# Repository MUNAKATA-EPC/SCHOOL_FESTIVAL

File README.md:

# SCHOOL_FESTIVAL
文化祭で使用したプログラムです

PS3コントローラーの受信に関して

http://gijin77.blog.jp/archives/21966552.html

上記のWEBサイトを参考にしました。使用するESP32ライブラリに関してVer1.0.4以外のバージョンで動作確認が取れません。専用ソフトを使用して使用するM5stampのMACaddressをコントローラーに書き込む必要があります。Ps3.data.---の戻り値がスティックの角度となります。

Wii Balance Bordに関して

https://github.com/takeru/Wiimote/tree/BalanceBoard

上記のWEBサイトを参考にしました。ライブラリをインストールしてサンプルプログラムを実行します。weight［ーーー］の戻り値が各センサの重量となります。起動時に本体裏のリセットボタンを押す必要があります。

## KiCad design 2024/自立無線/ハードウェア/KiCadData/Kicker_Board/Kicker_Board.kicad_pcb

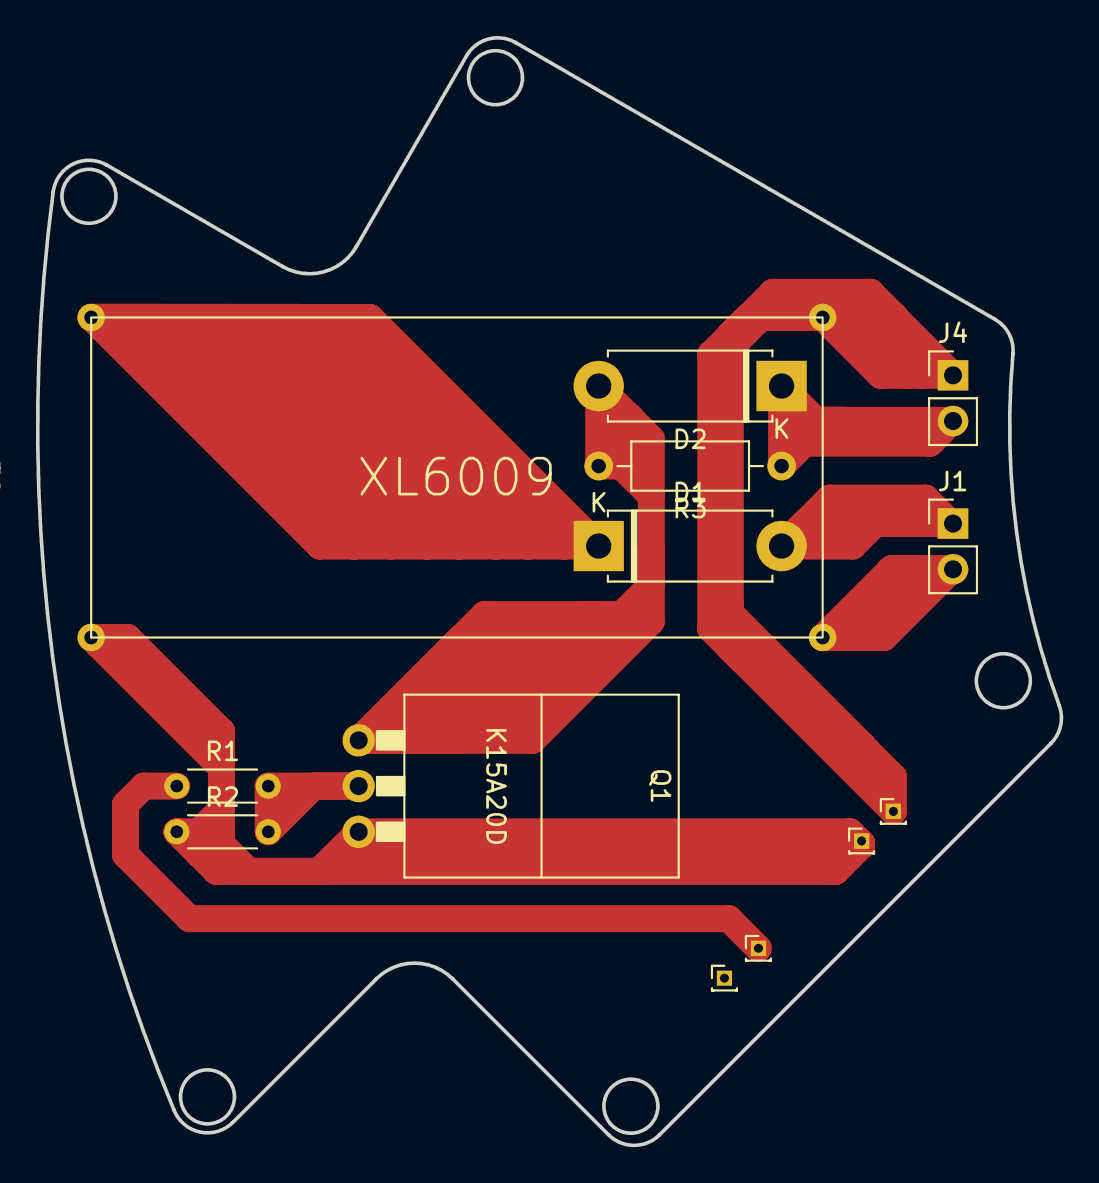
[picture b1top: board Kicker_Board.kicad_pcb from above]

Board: 2 copper layers, 56.9 x 61.5 mm, 9 parts (0 on the bottom side), 7 nets.

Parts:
D1, D2: D; D_5W_P10.16mm_Horizontal
J1, J4: Conn_01x02_Socket; PinHeader_1x02_P2.54mm_Vertical
Q1: NMOS; K15A20D
R1, R2: R; R_Axial_DIN0204_L3.6mm_D1.6mm_P5.08mm_Horizontal
R3: R; R_Axial_DIN0207_L6.3mm_D2.5mm_P10.16mm_Horizontal
U1: XL6009

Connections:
+12V: D1.2 (A), J1.1
GND: J1.2, Q1.3 (S), R2.1, U1.2 (IN-), U1.4 (OUT-)
unnamed: D1.1 (K), U1.1 (IN+)
unnamed: D2.2 (A), Q1.1 (D), R3.2
unnamed: D2.1 (K), J4.2, R3.1
unnamed: J4.1, U1.3 (OUT+)
unnamed: Q1.2 (G), R1.2, R2.2

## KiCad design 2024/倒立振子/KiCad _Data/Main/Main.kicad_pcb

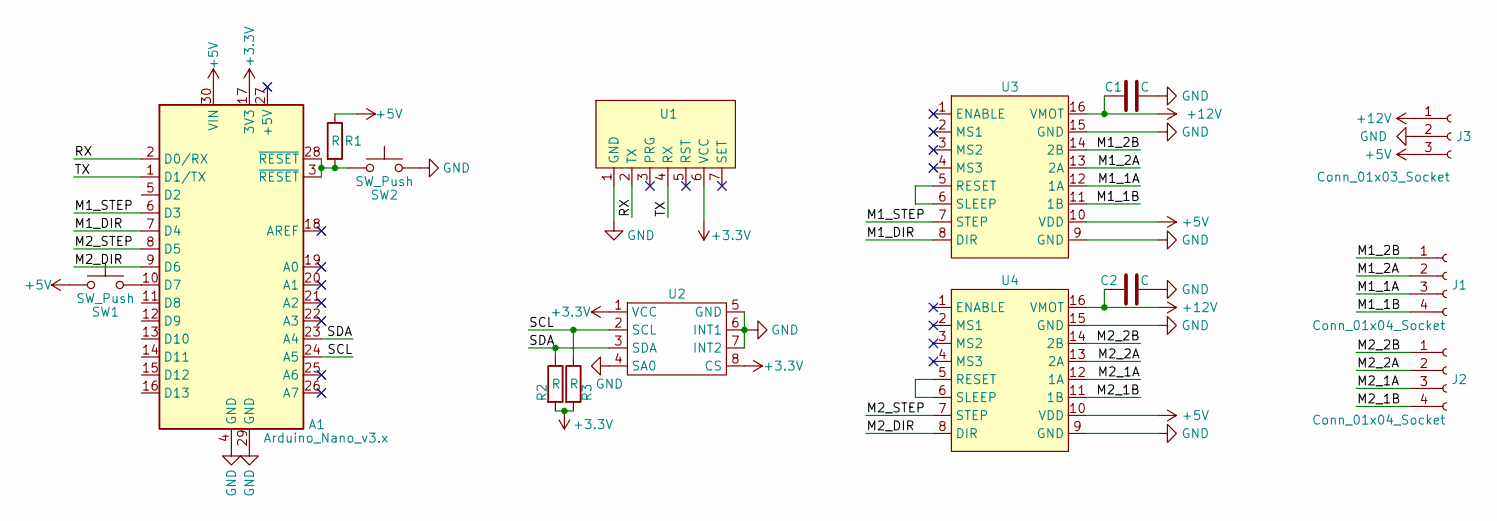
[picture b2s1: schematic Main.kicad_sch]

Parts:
A1: Arduino_Nano_v3.x; Arduino_Nano
C1, C2: C; CP_Radial_D5.0mm_P2.50mm
J1, J2: Conn_01x04_Socket; JST_XH_B4B-XH-A_1x04_P2.50mm_Vertical
J3: Conn_01x03_Socket; JST_XH_B3B-XH-A_1x03_P2.50mm_Vertical
R1, R2, R3: R; R_Axial_DIN0204_L3.6mm_D1.6mm_P5.08mm_Horizontal
SW1, SW2: SW_Push; SW_PUSH_6mm
U1: PinHeader_1x07_P2.54mm_Horizontal
U2: L3GD20H_Module
U3, U4: A4988

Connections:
+3.3V: A1.17 (3V3), R2.2, R3.2, U1.6 (VCC), U2.1 (VCC), U2.8 (CS)
+5V: A1.30 (VIN), J3.3, R1.1, SW1.1, U3.10 (VDD), U4.10 (VDD)
+12V: C1.2, C2.2, J3.1, U3.16 (VMOT), U4.16 (VMOT)
/M1_1A: J1.3, U3.12 (1A)
/M1_1B: J1.4, U3.11 (1B)
/M1_2A: J1.2, U3.13 (2A)
/M1_2B: J1.1, U3.14 (2B)
/M1_DIR: A1.7 (D4), U3.8 (DIR)
/M1_STEP: A1.6 (D3), U3.7 (STEP)
/M2_1A: J2.3, U4.12 (1A)
/M2_1B: J2.4, U4.11 (1B)
/M2_2A: J2.2, U4.13 (2A)
/M2_2B: J2.1, U4.14 (2B)
/M2_DIR: A1.9 (D6), U4.8 (DIR)
/M2_STEP: A1.8 (D5), U4.7 (STEP)
/RX: A1.2 (D0/RX), U1.2 (TX)
/SCL: A1.24 (A5), R3.1, U2.2 (SCL)
/SDA: A1.23 (A4), R2.1, U2.3 (SDA)
/TX: A1.1 (D1/TX), U1.4 (RX)
GND: A1.4 (GND), A1.29 (GND), C1.1, C2.1, J3.2, SW2.2, U1.1 (GND), U2.4 (SA0), U2.5 (GND), U2.6 (INT1), U2.7 (INT2), U3.9 (GND), U3.15 (GND), U4.9 (GND), U4.15 (GND)
unnamed: A1.10 (D7), SW1.2
unnamed: A1.3 (~RESET), A1.28 (~RESET), R1.2, SW2.1
unnamed: U3.5 (RESET), U3.6 (SLEEP)
unnamed: U4.5 (RESET), U4.6 (SLEEP)

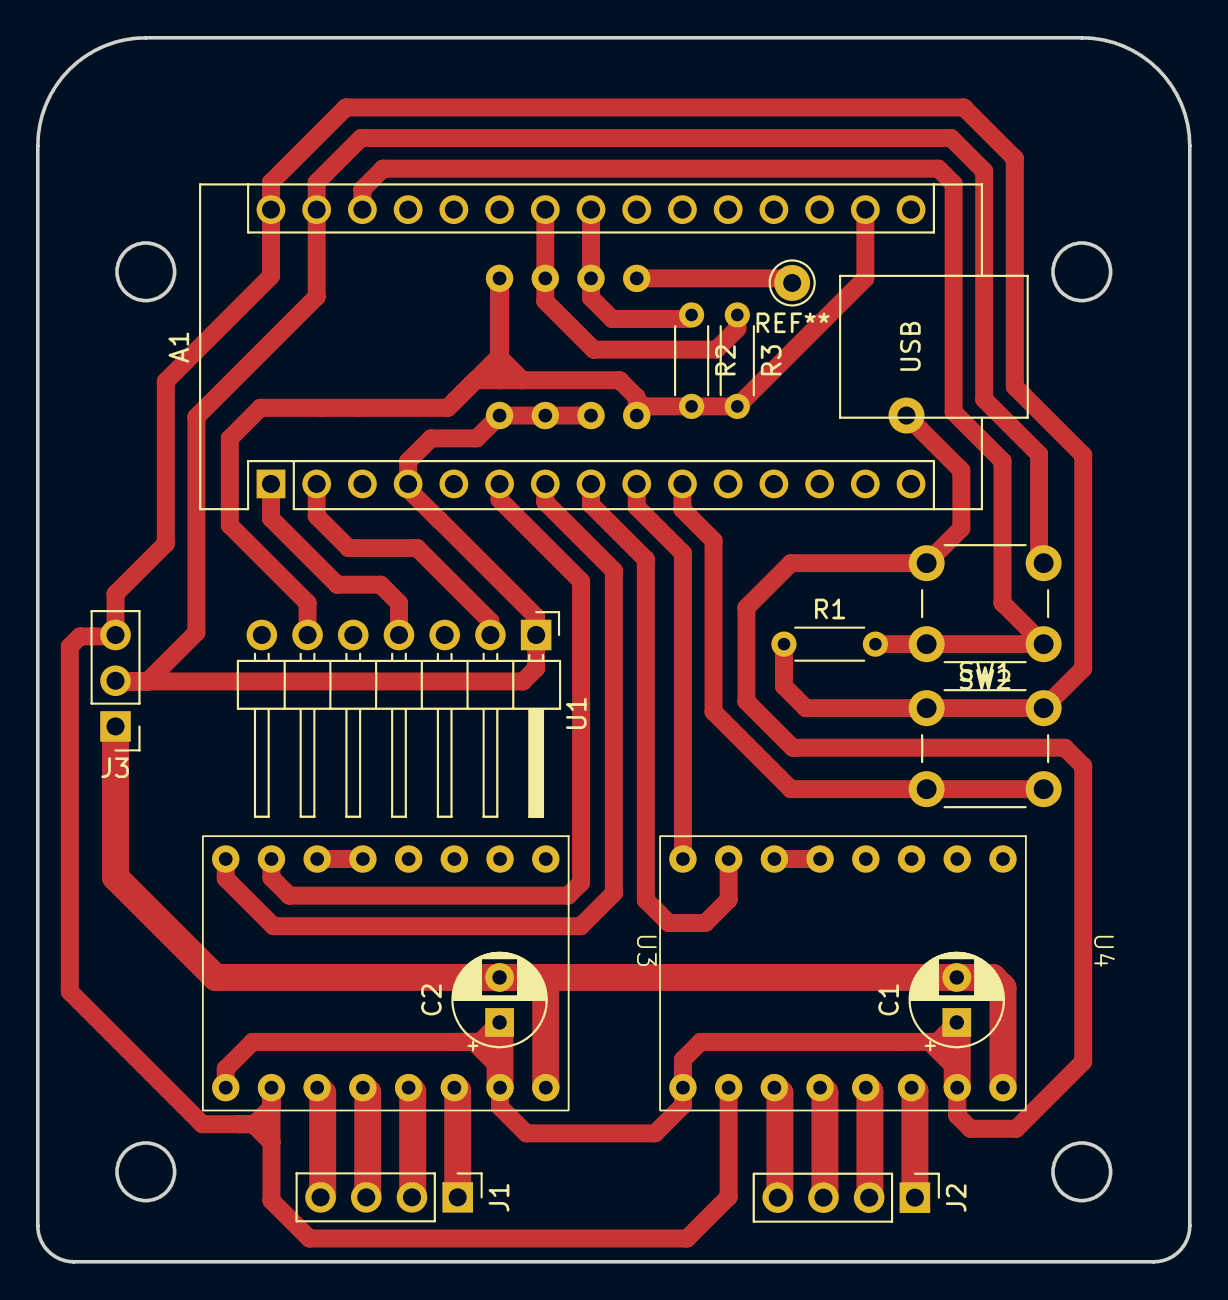
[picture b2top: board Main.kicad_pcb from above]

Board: 2 copper layers, 64.0 x 68.0 mm, 15 parts (1 on the bottom side), 24 nets.

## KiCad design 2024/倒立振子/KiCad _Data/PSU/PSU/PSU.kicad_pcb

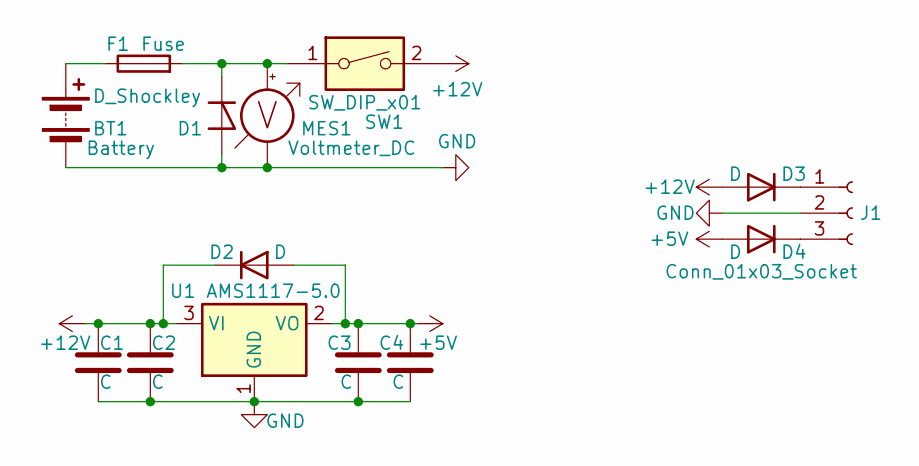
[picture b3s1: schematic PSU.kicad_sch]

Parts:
BT1: Battery; JST_VH_B2P-VH_1x02_P3.96mm_Vertical
C1, C4: C; CP_Radial_D5.0mm_P2.50mm
C2, C3: C; C_Disc_D3.0mm_W1.6mm_P2.50mm
D1: D_Shockley; D_5W_P10.16mm_Horizontal
D2, D3, D4: D; D_A-405_P7.62mm_Horizontal
F1: Fuse; fuse_socket
J1: Conn_01x03_Socket; JST_XH_S3B-XH-A_1x03_P2.50mm_Horizontal
MES1: Voltmeter_DC; voltage_counter
SW1: SW_DIP_x01; DS-850k
U1: AMS1117-5.0; TO-220-3_Horizontal_TabDown

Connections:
+5V: C3.1, C4.1, D2.2 (A), D4.2 (A), U1.2 (VO)
+12V: C1.1, C2.1, D2.1 (K), D3.2 (A), SW1.2, U1.3 (VI)
GND: BT1.2 (-), C1.2, C2.2, C3.2, C4.2, D1.2 (A), J1.2, MES1.1 (-), U1.1 (GND)
unnamed: BT1.1 (+), F1.1
unnamed: D1.1 (K), F1.2, MES1.2 (+), SW1.1
unnamed: D3.1 (K), J1.1
unnamed: D4.1 (K), J1.3

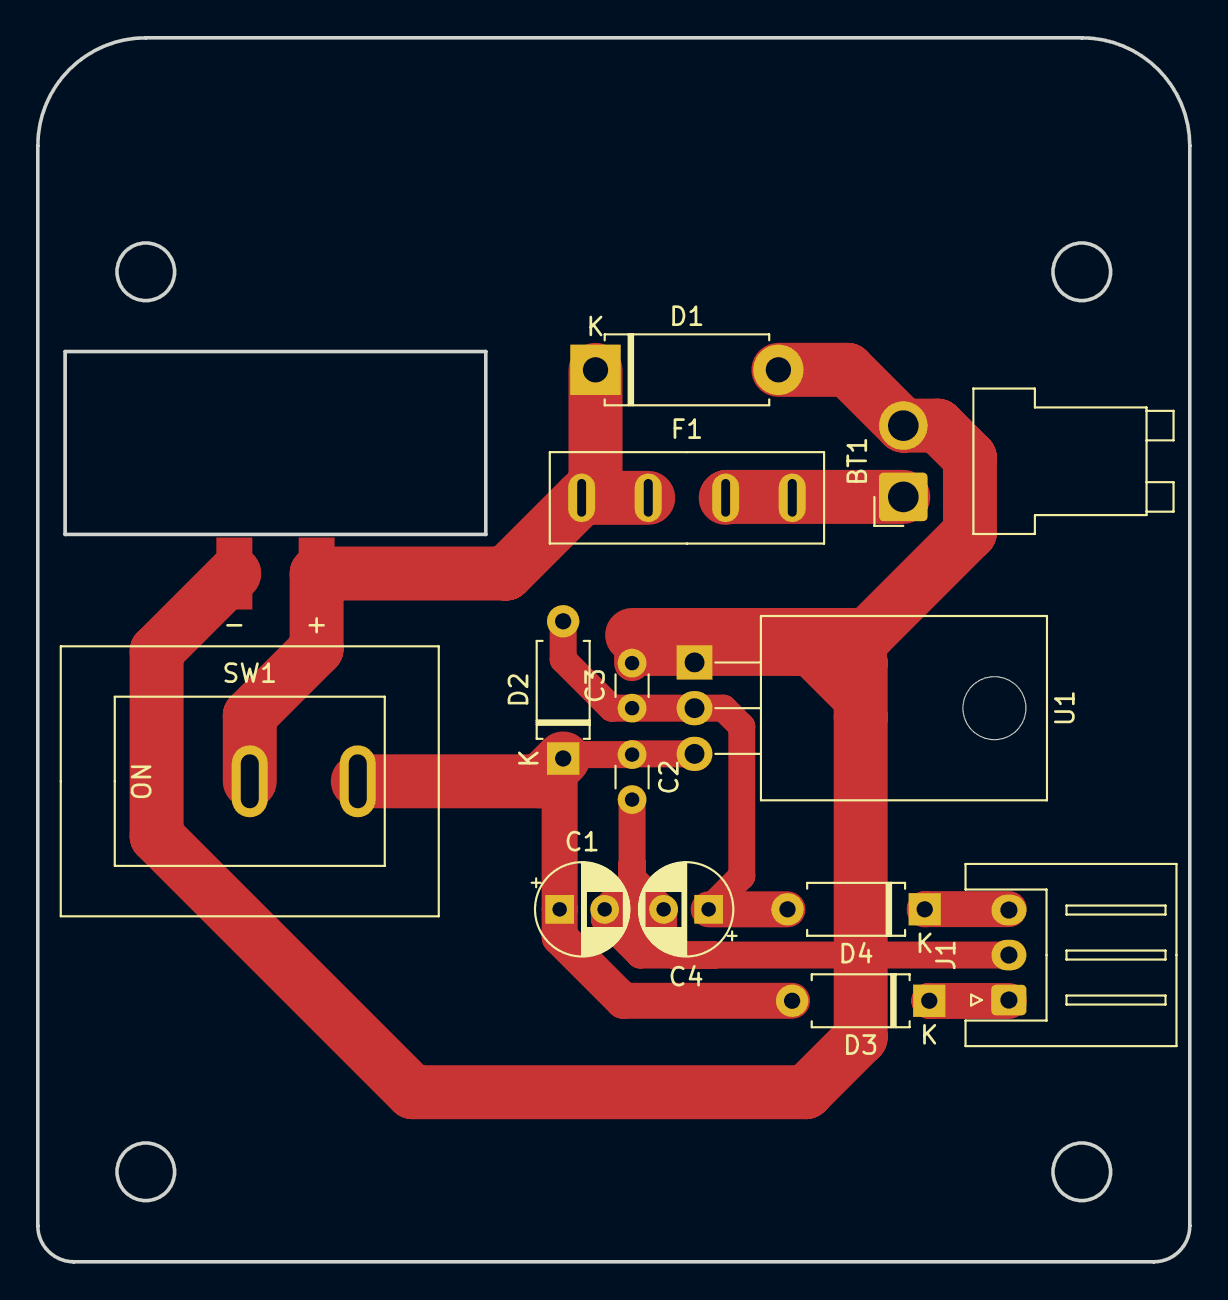
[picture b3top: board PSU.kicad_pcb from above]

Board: 2 copper layers, 64.0 x 68.0 mm, 14 parts (1 on the bottom side), 7 nets.

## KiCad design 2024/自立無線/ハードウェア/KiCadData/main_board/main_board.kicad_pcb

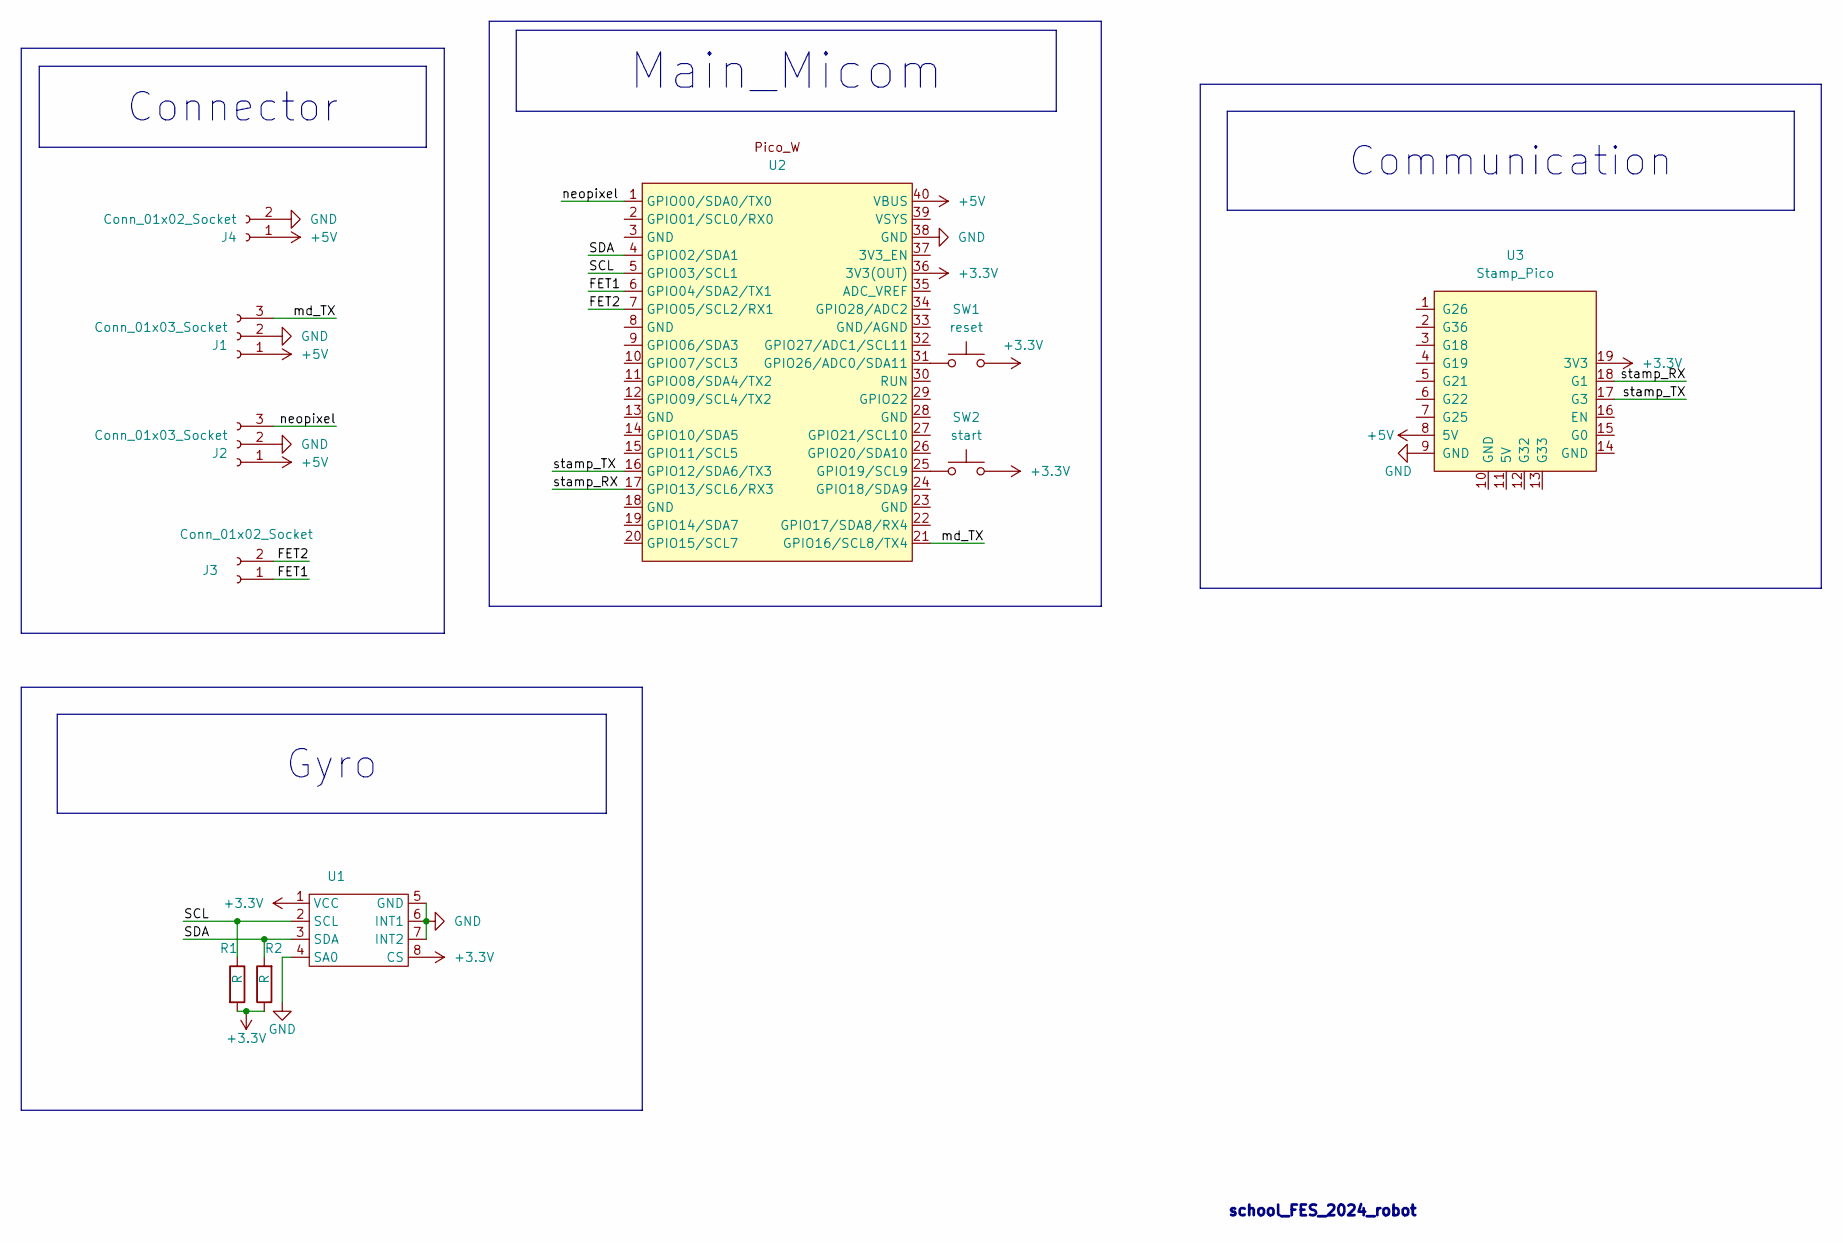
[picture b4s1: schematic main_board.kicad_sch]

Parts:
J1: Conn_01x03_Socket; JST_XH_S3B-XH-A_1x03_P2.50mm_Horizontal
J2: Conn_01x03_Socket; JST_XH_B3B-XH-A_1x03_P2.50mm_Vertical
J3, J4: Conn_01x02_Socket; JST_XH_S2B-XH-A_1x02_P2.50mm_Horizontal
R1, R2: R; R_Axial_DIN0204_L3.6mm_D1.6mm_P5.08mm_Horizontal
SW1: reset; SW_PUSH-12mm_Wuerth-430476085716
SW2: start; SW_PUSH-12mm_Wuerth-430476085716
U1: L3GD20H_Module_KiCad6.0
U2: Pico_W
U3: Stamp_Pico; StampPico_template

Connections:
+3.3V: R1.2, R2.1, SW1.2, SW2.2, U1.1 (VCC), U1.8 (CS), U2.36 (3V3(OUT)), U3.19 (3V3)
+5V: J1.1, J2.1, J4.1, U2.40 (VBUS), U3.8 (5V)
/FET1: J3.1, U2.6 (GPIO04/SDA2/TX1)
/FET2: J3.2, U2.7 (GPIO05/SCL2/RX1)
/SCL: R1.1, U1.2 (SCL), U2.5 (GPIO03/SCL1)
/SDA: R2.2, U1.3 (SDA), U2.4 (GPIO02/SDA1)
/md_TX: J1.3, U2.21 (GPIO16/SCL8/TX4)
/neopixel: J2.3, U2.1 (GPIO00/SDA0/TX0)
/stamp_RX: U2.17 (GPIO13/SCL6/RX3), U3.18 (G1)
/stamp_TX: U2.16 (GPIO12/SDA6/TX3), U3.17 (G3)
GND: J1.2, J2.2, J4.2, U1.4 (SA0), U1.5 (GND), U1.6 (INT1), U1.7 (INT2), U2.38 (GND), U3.9 (GND)
unnamed: SW2.1, U2.25 (GPIO19/SCL9)
unnamed: SW1.1, U2.31 (GPIO26/ADC0/SDA11)

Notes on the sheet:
Main_Micom
Communication
Connector
Gyro
school_FES_2024_robot

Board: 2 copper layers, 11 parts (0 on the bottom side), 13 nets, no tracks yet.

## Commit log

2022-05-31 文化祭で使用したコードのアップロード
2022-06-01 グローバルビジョン表示用
2023-04-14 For 2023 Season
2024-04-08 Create txt
2024-04-14 first
2024-04-15 test
    test.
2024-04-16 test
    test
2024-04-16 data organized
2024-04-17 ライブラリ追加
    StampPICOのライブラリ追加
2024-04-21 あばば
    あ〜〜〜〜
2024-04-21 基板の外径データ
2024-04-21 とりあえずテスト
2024-04-22 今日の進捗
    あああああああああああああ
2024-04-24 基板データの更新
2024-05-19 色々
    ああああああああああああ
2024-06-09 あああああああ
